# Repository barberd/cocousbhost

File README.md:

# CoCo USB Host

## Description

This board is a cartridge for the Tandy Radio Shack TRS-80 Color Computer (CoCo), an 8 bit computer produced between 1980 and 1991. It provides a USB 2.0 Host controller, the CH376S, to the CoCo. This allows one to use USB devices with the Color Computer given software drivers for the device. See "Using the Board" below.

Schematic is available [here](kicad/cocousbhost.pdf).

Assembly routines for using the cartridge in your own software can be found in the [Software](Software) directory. This includes drivers for USB hubs, keyboards, mice, and mass storage devices (such as pendrives). Additionally, a software patch for the Color Computer 3's BASIC to use a USB keyboard for input can be found in this directory.

## Building the board

This is open source hardware, so its up to one to get the board fabricated and then solder the components onto it. All components are through-hole-mount for easy assembly by hobbyists, with the exception of the CH376S chip itself; that requires surface mount soldering. 

If you've done soldering but are new to surface mounting chips: pin the chip into place by soldering two opposite corner pins, then with a hot iron and plenty of flux, run a bead of solder down each side, then wick up any excess.

### How to order for fabrication

Download [kicad/cocousbhost-fabrication.zip](kicad/cocousbhost-fabrication.zip?raw=true), then upload it to one's PCB manufacturer when asked to provide Gerber files. Usually this is found under a 'Quote' option on the website. Search "pcb manufacturing" on any major search engine to get several manufacturers. NextPCB and PCBWay are two well-known ones.

Some may have ordered boards and have extra available. Reach out to don &#x40; dgb3.net to explore this.

Use the [Bill of Materials](kicad/cocousbhost.csv) to source the components from electronic supply houses such as Mouser, Jameco, or Digi-Key.

## Source and License

Design maintained at [https://github.com/barberd/cocousbhost](https://github.com/barberd/cocousbhost). [Kicad](https://www.kicad.org/) and [Freerouting](https://github.com/freerouting/freerouting/) were used to design the board.

The design is copyright 2025 by Don Barber. The design is open source, distributed via the GNU GPL version 3 license. Please see the COPYING file for details.

## Why

In 2022 I developed the [CoCo USB Serial Pak](https://github.com/barberd/cocousbserial), a cartridge that looks like an original Tandy Deluxe RS-232 pak to the CoCo but instead presents as a USB serial device to the PC its plugged into. That cartridge allows for very fast and easy communication between the CoCo and PC (think of it as a null modem cable), but does not provide any ability to host USB devices, to the confusion of many in the CoCo community.

After that project, I wanted to produce a cartridge that did provide that USB host ability for the CoCo. I also didn't want to just interface to another computer (such as a Raspberry Pi Pico or ESP) that does the real USB work; I wanted the CoCo to control the USB bus and communicate with devices directly, recognizing I'd have to write software drivers from scratch. This is the result.

## Using the Board

Please do not expect to use this board as a drop-in to replace the Color Computer's keyboard, joysticks, storage mediums, or other hardware and expect all the original software to work immediately and transparently.

This board provides a USB bus for the Color Computer. Use of that bus, and any devices found on that bus, requires software drivers. Patches for the original DECB routines for POLCAT (read a character from the keyboard) to use a USB keyboard is available in the Software directory. These DECB patches work with most Basic programs and any machine language software coded to use DECB's built-in routines.

Conceptually, a similar patch for DECB's JOYIN (read from the Joysticks) routine can be developed, but as joysticks do not have a standard report format (unlike keyboard and mice Boot protocol), each joystick model will need a custom driver developed. But if developed, this would work for Basic programs and those machine language software packages that use the JOYIN routine.

However, the majority of original applications and games are hard-coded to access the keyboard, joystick, and serial devices directly through the Peripheral Interface Adapter (PIA) chips of the CoCo and not through DECB's provided routines. If one desires, one can patch such software to instead leverage USB devices through this cartridge, but each software package is a custom effort. One can leverage the routines and drivers in the Software directory as a starting point.

The exception for needing to patch software is when software is running under an operating system (where hardware is abstracted away through an API) and that operating system has USB drivers; the operating system's programming interface in combination with drivers takes care of the hardware interfacing. There are a few operating system available for the CoCo; see the "NitrOS-9" section below for one implementation.

To digress from this cartridge slightly: If one wants to use USB devices transparently with old software without patching, one will instead need a hardware solution that plugs directly into the original hardware's interface, presenting translated signals in a way the original software expects. This is normally done with a second computer (such as an Arduino, ESP, or Raspberry Pi Pico) doing the USB communication, converting the signal information, and then re-presenting such via the legacy interface (such as plugging into the keyboard matrix ribbon connector plug or the joystick port). See [USB to CoCo Keyboard Adapter](https://thebreakkey.com/projects.html), [PiKey](http://www.pikey.tech/), and [CocoJoyStickAdapter](https://github.com/malfunct/CocoJoystickAdapter) for examples. The [CoCoSDC](http://cocosdc.blogspot.com/) uses a similar technique with an Atmel microprocessor (though for a SD card interface, not a USB device). All these solutions are brilliant; they provide drop-in solutions requiring no change to legacy software.

The intent of this cartridge is different: unlike these hardware-interfacing solutions, this USB host cartridge provides a full USB bus to the CoCo. This means by writing new drivers, one can use any USB device, including those not originally available on the CoCo. This could include scanners, printers, webcams, network adapters, bluetooth adapters, light guns, sound adapters, digitizer drawing tablets, etc; almost any USB device can be made to work. This provides diverse flexibility for a CoCo developer to write new software leveraging a wide range of available hardware; homebrew is still alive and well for the CoCo!

Two limitations to be aware: 

  * The CH376 chip does not support isochronous USB transfers (this means some of the streaming protocols often used on sound adapters and newer webcams won't work, though many webcams still support the interrupt and bulk transfer methods as well) 
  * The CoCo itself might be too slow for some USB devices - its bus speed can only transfer data so quickly.

### Configuration

Set the 7 dip switches (SW1) for the desired base IO address. These correspond to address lines A1 through A7. The default is $FF86. See [here](https://www.cocopedia.com/wiki/index.php/External_Hardware_IO_Address_Map) for a list of known IO hardware addresses. If you happen to have a conflict, choose a different IO address, set SW1 accordingly, and reassemble binaries to match.

The orientation of SW1 matters; it should be that the 'circuit is closed' or 'on' direction points to the 0 side. This is because the 74LS682 chip works by defaulting to '1' unless pulled to ground to make it a '0'. This simplifies and lowers the cost of the address selection circuit but also results in the non-intuitive use of 'on' to get a '0' instead of a '1'.

As such, make sure to orient the switch to match 'on' to face the same direction as the '0' label. If one gets the switch upside down, not a big deal, the switch will just operate in reverse from the silkscreened labels.

### Overview

The cartridge uses two memory-mapped ports, the base address and the base address+1. The two addresses used correspond to different registers on the CH376 and board. For example, if given base address of $FF86:

  * $FF86 Data Register (Read and Write)
  * $FF87 Command Register (Write) and Flag Register (Read)

Read the [CH376 Datasheet 1](datasheets/CH376DS1.PDF?raw=true) and [CH376 Datasheet 2](datasheets/CH376DS2.PDF?raw=true) for how to use the chip.

The CH376 chip has built-in commands to access USB mass storage devices both at the block level and file level. The CH376 also allows for control transfers (used to configure devices), interrupt transfers (used for keyboards, mice, game controllers, etc), and bulk storage transfers (used for mass storage such as pendrives). It does not support isochronous transfers (used for streaming data), so it will not work with some modern sound adapters and webcam protocols.

Note that the CH376 can only connect directly to a single USB device. That device can be a USB Hub, but this means driver software must configure the hub to allow communication to other devices through it. Such a driver can be found in the Software directory. Its HIGHLY recommended to use a powered USB hub; otherwise the USB devices will draw power from the Color Computer or Multi-Pak interface.

### Interrupts

The CH376 will issue an interrupt after completing several commands. This will assert the CART\* line on the cartridge. When PIA1 is configured to do so, a fast interrupt request (FIRQ) is sent to the CPU when CART\* goes low.

To configure the PIA1 to do this, enable fast interrupts and configure it to trigger on a falling edge, like so:

                LDA     $FF23           ;load PIA1 Side B Control Register
                ORA     #$01            ;set bit 0 to 1 to enable cart firq
                ANDA    #$FD            ;set bit 1 to 0 to trigger on falling-edge
                STA     $FF23           ;store in PIA1 Side B Control Register

Hook in the interrupt handler at $010F (and/or $FEF4 on the CoCo3) as one would any other FIRQ handler. Make sure the interrupt handler performs a GET_STATUS to clear the interrupt.

If one's software doesn't handle interrupts, one will need to use software polling of the flag register instead.

See the routines in the Software directory for examples.

### ROM Socket

A socket for a ROM is also included in the board design. This is entirely optional, as many users today will instead choose to use another boot device, such as disk, SDC, or DriveWire. However, one can add a ROM loaded with a bootloader, perhaps to boot NitrOS-9 directly off a USB drive (see the "NitrOS-9" section below) or patching BASIC for USB drives and keyboards.

The ROM socket is wired for a 27128 EPROM. As the 27128 provides 16k of storage, the board presents this as 2 different banks of 8k each, selected via jumper J1. As such, when writing the EPROM, combine the images with each image aligned to an 8k boundary (eg, at 0 and 8k). If using a ROM IC other than the 27128, one will need to adjust the board design to match the chosen IC. Some other ROM ICs are pin-compatible and will work fine with the existing design.

Note Jumper J2, labeled "Autostart ROM". Color Computer cartridges signal the onboard ROM that they are present and should be started on boot by shorting the Q signal to the CART\* signal; see [Tandy Cartridge Schematic](https://colorcomputerarchive.com/repo/Documents/Manuals/Hardware/Color%20Computer%20ROM%20Cartridge%20Schematic%20%28Tandy%29.pdf). This works great for end users as game cartridges will auto-start, but this technique conflicts for device cartridges which need to also send interrupts. This is evident in cartridges like the [Tandy Deluxe RS-232 pak](https://colorcomputerarchive.com/repo/Documents/Manuals/Hardware/Deluxe%20RS-232%20Program%20Pak%20Schematic%20%28Tandy%29.pdf), wherein users had to execute the ROM manually by running "exec &hc000" (Color Computer 1 or 2) or "exec &he010" (Color Computer 3) to start their software.

Through the use of a flipflop and some additional logic, this cartridge attempts to allow auto-start while also allowing the CH376 to send interrupts after bootup: if the J2 jumper is present, then on startup, the Q signal is sent to CART\*, like any auto-start cartridge. However, once the ROM is accessed, this signal is gated off, so normal interrupts from the CH376 can be sent. This works perfectly if booting from the cartridge and allows for both auto-start and use of the CH376 interrupts.

However, if one has the J2 jumper present but boots via another method (perhaps via a floppy drive or a CocoSDC in another selected multi-pak interface slot), then the ROM is never accessed and the Q signal will continue to be asserted to CART\*. This will prevent proper use of interrupts. If one is not using the auto-start feature, remove the J2 jumper to prevent this contention.

If one never plans on using the ROM, one can eliminate components J1, J2, U7, U5, R4, and Q1.

## More Info

### NitrOS-9

[NitrOS-9](https://github.com/nitros9project/nitros9) is a community maintained open source operating system for the Color Computer based on Microware's OS9. Several modules have been written for NitrOS-9 providing a USB Manager and drivers for various USB devices (such as mass storage devices, keyboards, and mice). Additionally, a boot module is available that boots NitrOS-9 directly off a pen drive connected to this cartridge when written to a ROM in the ROM socket.

### Links

* [CH376 Datasheet 1](datasheets/CH376DS1.PDF?raw=true)
* [CH376 Datasheet 2](datasheets/CH376DS2.PDF?raw=true)
* [USB 2.0 Specification](https://www.usb.org/document-library/usb-20-specification) Useful for various control transfer protocols
* [USB HID Class Definition](https://www.usb.org/sites/default/files/documents/hid1_11.pdf) Useful Keyboard and Mouse boot protocols
* [USB Printer Device Class Definition](https://www.usb.org/sites/default/files/usbprint11a021811.pdf) 
* [USB Mass Storage Specification](https://www.usb.org/sites/default/files/Mass_Storage_Specification_Overview_v1.4_2-19-2010.pdf)
* [USB Mass Storage Bulk-Only Transport](https://www.usb.org/sites/default/files/usbmassbulk_10.pdf)
* [SCSI Command Reference (from Seagate)](https://www.seagate.com/files/staticfiles/support/docs/manual/Interface%20manuals/100293068j.pdf) USB Mass storage devices use encapsulated SCSI
* [Color Computer Technical Reference](https://colorcomputerarchive.com/repo/Documents/Manuals/Hardware/Color%20Computer%20Technical%20Reference%20Manual%20%28Tandy%29.pdf) See Page 18 of the manual/25 of the PDF for bus timings.

### Note on the CH375B versus CH376S

The CH375 is a very similar chip that provides the same USB functionality of the CH376. The CH376 also costs slightly more and its additional features (interfacing with an SD card controller) are not used on this cartridge. Therefore, one might be tempted to use a CH375 instead. 

In the author's experience, the CH375 has an undocumented bug that drops a byte seemingly at random, leading to corrupted data and trouble keeping software and hardware in sync. This behavior was consistent across four chips the author tested, and seems consistent with anecdotal user experiences found online around other solutions using the CH375, such as ISA cards designed for early PCs.

If one does choose to use the CH375B instead, either add a bodge wire or modify the design before manufacturing to connect pin 23 to ground, and use $2B (WR_USB_DATA7) for the write command instead of $2C (WR_HOST_DATA).

## Errata

None at this time.

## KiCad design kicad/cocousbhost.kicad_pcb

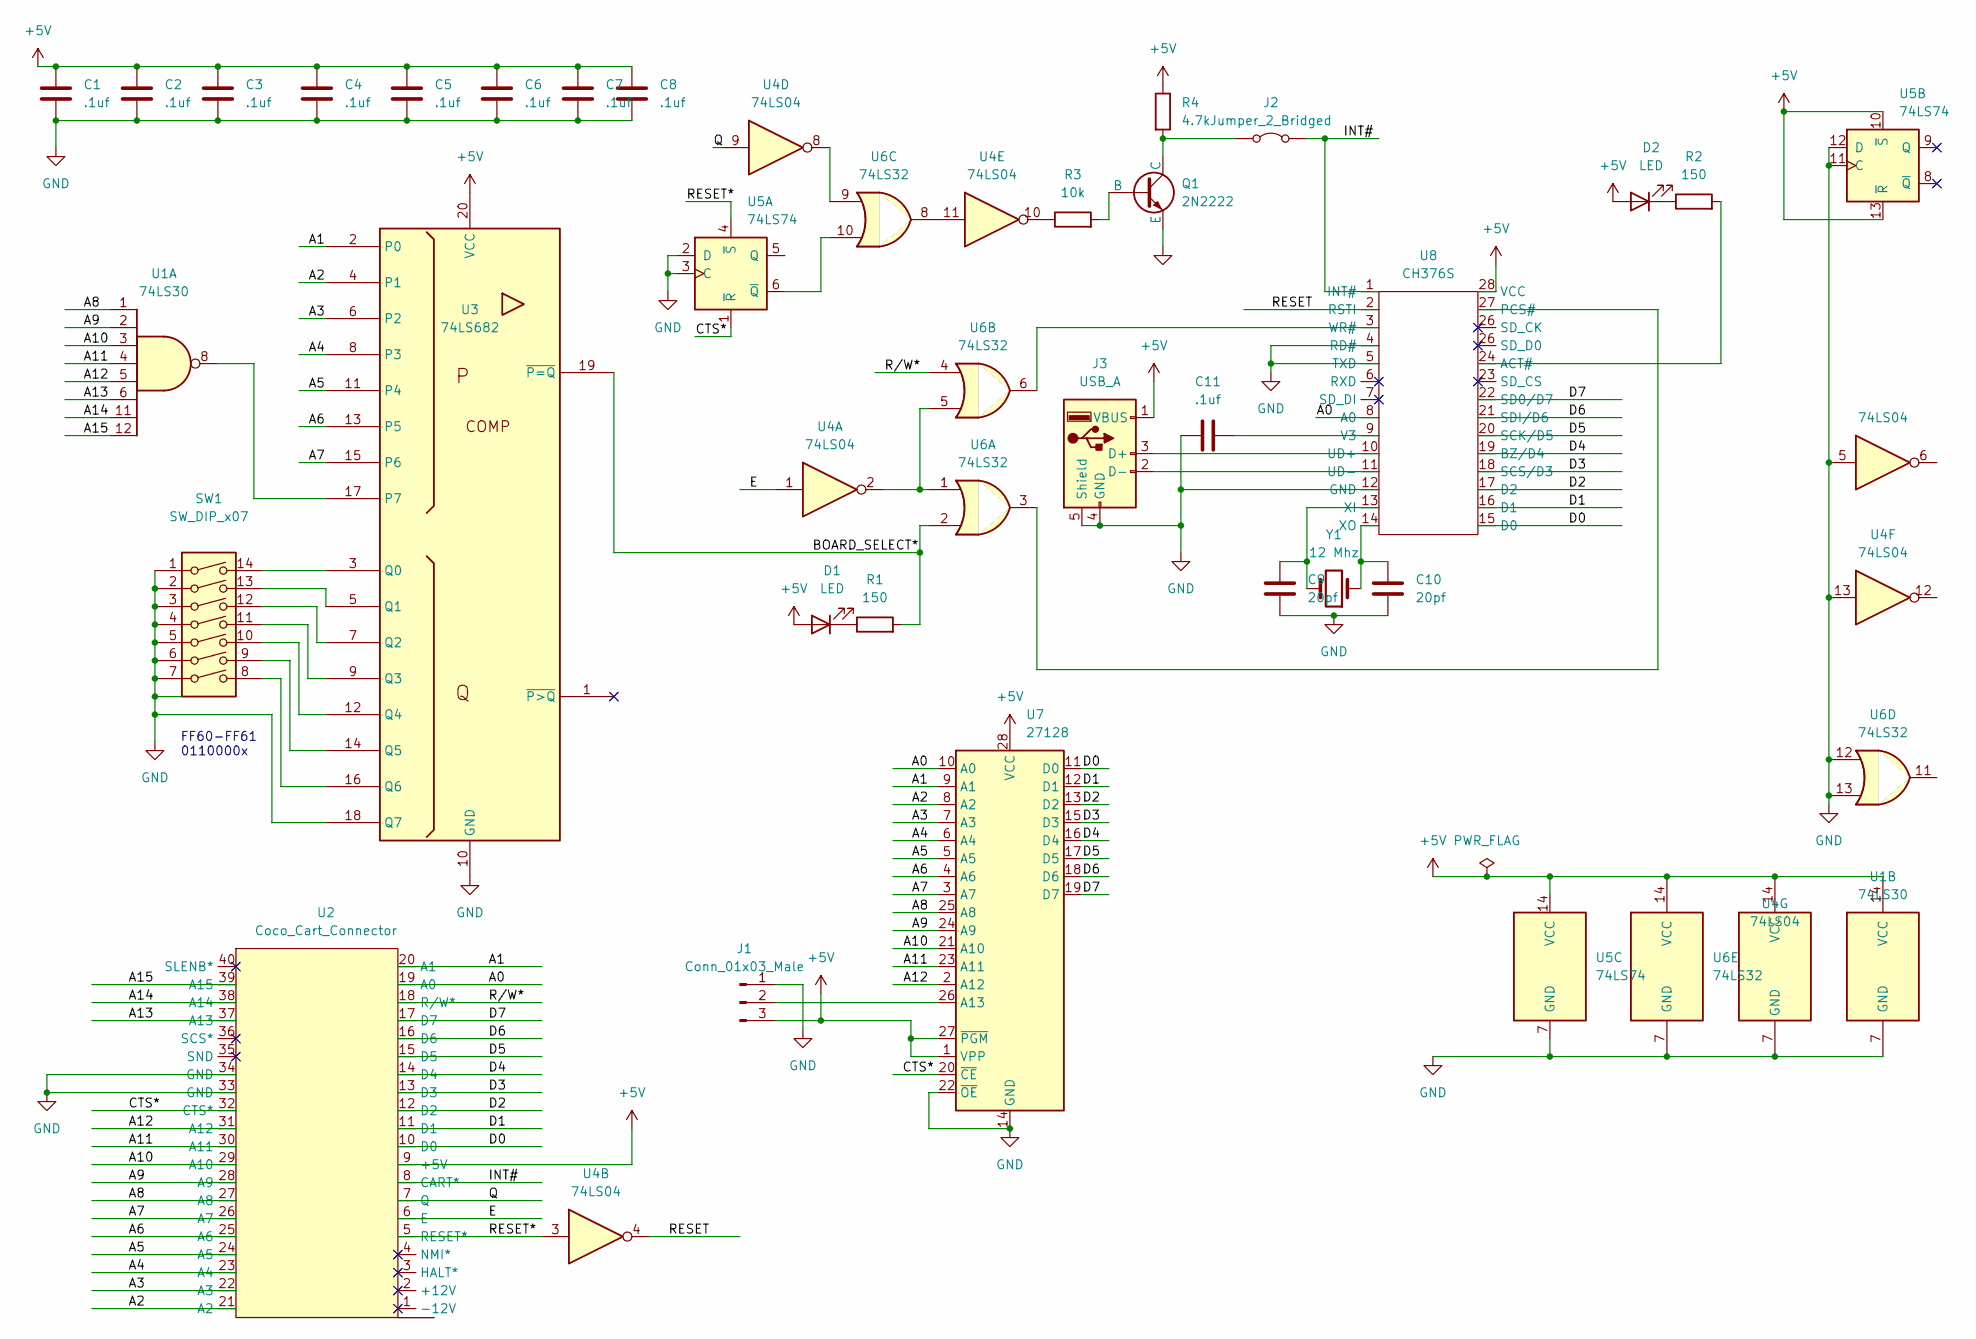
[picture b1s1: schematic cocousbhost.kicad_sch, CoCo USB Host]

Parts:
C1, C2, C3, C4, C5, C6, C7, C8, C11: .1uf; C_Disc_D6.0mm_W2.5mm_P5.00mm
C9, C10: 20pf; C_Disc_D6.0mm_W2.5mm_P5.00mm
D1, D2: LED; LED_D3.0mm
J1: Conn_01x03_Male; PinHeader_1x03_P2.54mm_Vertical
J2: Jumper_2_Bridged; PinHeader_1x02_P2.54mm_Vertical
J3: USB_A; USB_A_Molex_67643_Horizontal
Q1: 2N2222; TO-92
R1, R2: 150; R_Axial_DIN0204_L3.6mm_D1.6mm_P7.62mm_Horizontal
R3: 10k; R_Axial_DIN0204_L3.6mm_D1.6mm_P7.62mm_Horizontal
R4: 4.7k; R_Axial_DIN0204_L3.6mm_D1.6mm_P7.62mm_Horizontal
SW1: SW_DIP_x07; SW_DIP_SPSTx07_Slide_6.7x19.34mm_W7.62mm_P2.54mm_LowProfile
U1: 74LS30; DIP-14_W7.62mm
U2: Coco_Cart_Connector; Coco_Cart
U3: 74LS682; DIP-20_W7.62mm
U4: 74LS04; DIP-14_W7.62mm
U5: 74LS74; DIP-14_W7.62mm
U6: 74LS32; DIP-14_W7.62mm
U7: 27128; DIP-28_W15.24mm
U8: CH376S; SOP-28
Y1: 12 Mhz; Crystal_HC52-8mm_Vertical

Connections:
+5V: C1.1, C2.1, C3.1, C4.1, C5.1, C6.1, C7.1, C8.1, D1.2 (A), D2.2 (A), J1.3, J3.1 (VBUS), R4.1, U1.14 (VCC), U2.9 (+5V), U3.20 (VCC), U4.14 (VCC), U5.10 (~S), U5.13 (~R), U5.14 (VCC), U6.14 (VCC), U7.1 (VPP), U7.27 (~PGM), U7.28 (VCC), U8.28 (VCC)
/A0: U2.19 (A0), U7.10 (A0), U8.8 (A0)
/A1: U2.20 (A1), U3.2 (P0), U7.9 (A1)
/A2: U2.21 (A2), U3.4 (P1), U7.8 (A2)
/A3: U2.22 (A3), U3.6 (P2), U7.7 (A3)
/A4: U2.23 (A4), U3.8 (P3), U7.6 (A4)
/A5: U2.24 (A5), U3.11 (P4), U7.5 (A5)
/A6: U2.25 (A6), U3.13 (P5), U7.4 (A6)
/A7: U2.26 (A7), U3.15 (P6), U7.3 (A7)
/A8: U1.1, U2.27 (A8), U7.25 (A8)
/A9: U1.2, U2.28 (A9), U7.24 (A9)
/A10: U1.3, U2.29 (A10), U7.21 (A10)
/A11: U1.4, U2.30 (A11), U7.23 (A11)
/A12: U1.5, U2.31 (A12), U7.2 (A12)
/A13: U1.6, U2.37 (A13)
/A14: U1.11, U2.38 (A14)
/A15: U1.12, U2.39 (A15)
/BOARD_SELECT*: R1.2, U3.19 (~P=Q), U6.2
/CTS*: U2.32 (CTS*), U5.1 (~R), U7.20 (~CE)
/D0: U2.10 (D0), U7.11 (D0), U8.15 (D0)
/D1: U2.11 (D1), U7.12 (D1), U8.16 (D1)
/D2: U2.12 (D2), U7.13 (D2), U8.17 (D2)
/D3: U2.13 (D3), U7.15 (D3), U8.18 (SCS/D3)
/D4: U2.14 (D4), U7.16 (D4), U8.19 (BZ/D4)
/D5: U2.15 (D5), U7.17 (D5), U8.20 (SCK/D5)
/D6: U2.16 (D6), U7.18 (D6), U8.21 (SDI/D6)
/D7: U2.17 (D7), U7.19 (D7), U8.22 (SD0/D7)
/E: U2.6 (E), U4.1
/INT#: J2.2 (B), U2.8 (CART*), U8.1 (INT#)
/Q: U2.7 (Q), U4.9
/RESET: U4.4, U8.2 (RSTI)
/RESET*: U2.5 (RESET*), U4.3, U5.4 (~S)
/R/W*: U2.18 (R/W*), U6.4
GND: C1.2, C2.2, C3.2, C4.2, C5.2, C6.2, C7.2, C8.2, C9.1, C10.1, C11.1, J1.1, J3.4 (GND), J3.5 (Shield), Q1.3 (E), SW1.1, SW1.2, SW1.3, SW1.4, SW1.5, SW1.6, SW1.7, U1.7 (GND), U2.33 (GND), U2.34 (GND), U3.10 (GND), U3.18 (Q7), U4.5, U4.7 (GND), U4.13, U5.2 (D), U5.3 (C), U5.7 (GND), U5.11 (C), U5.12 (D), U6.7 (GND), U6.12, U6.13, U7.14 (GND), U7.22 (~OE), U8.4 (RD#), U8.5 (TXD), U8.12 (GND)
unnamed: D1.1 (K), R1.1
unnamed: D2.1 (K), R2.1
unnamed: J1.2, U7.26 (A13)
unnamed: J2.1 (A), Q1.1 (C), R4.2
unnamed: J3.3 (D+), U8.10 (UD+)
unnamed: J3.2 (D-), U8.11 (UD-)
unnamed: Q1.2 (B), R3.2
unnamed: R3.1, U4.10
unnamed: U1.8, U3.17 (P7)
unnamed: SW1.14, U3.3 (Q0)
unnamed: SW1.13, U3.5 (Q1)
unnamed: SW1.12, U3.7 (Q2)
unnamed: SW1.11, U3.9 (Q3)
unnamed: SW1.10, U3.12 (Q4)
unnamed: SW1.9, U3.14 (Q5)
unnamed: SW1.8, U3.16 (Q6)
unnamed: U4.2, U6.1, U6.5
unnamed: U4.8, U6.9
unnamed: U4.11, U6.8
unnamed: U5.6 (~Q), U6.10
unnamed: R2.2, U8.24 (ACT#)
unnamed: U6.3, U8.27 (PCS#)
unnamed: C11.2, U8.9 (V3)
unnamed: U6.6, U8.3 (WR#)
unnamed: C9.2, U8.13 (XI), Y1.2
unnamed: C10.2, U8.14 (XO), Y1.1

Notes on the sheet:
FF60-FF61 0110000x

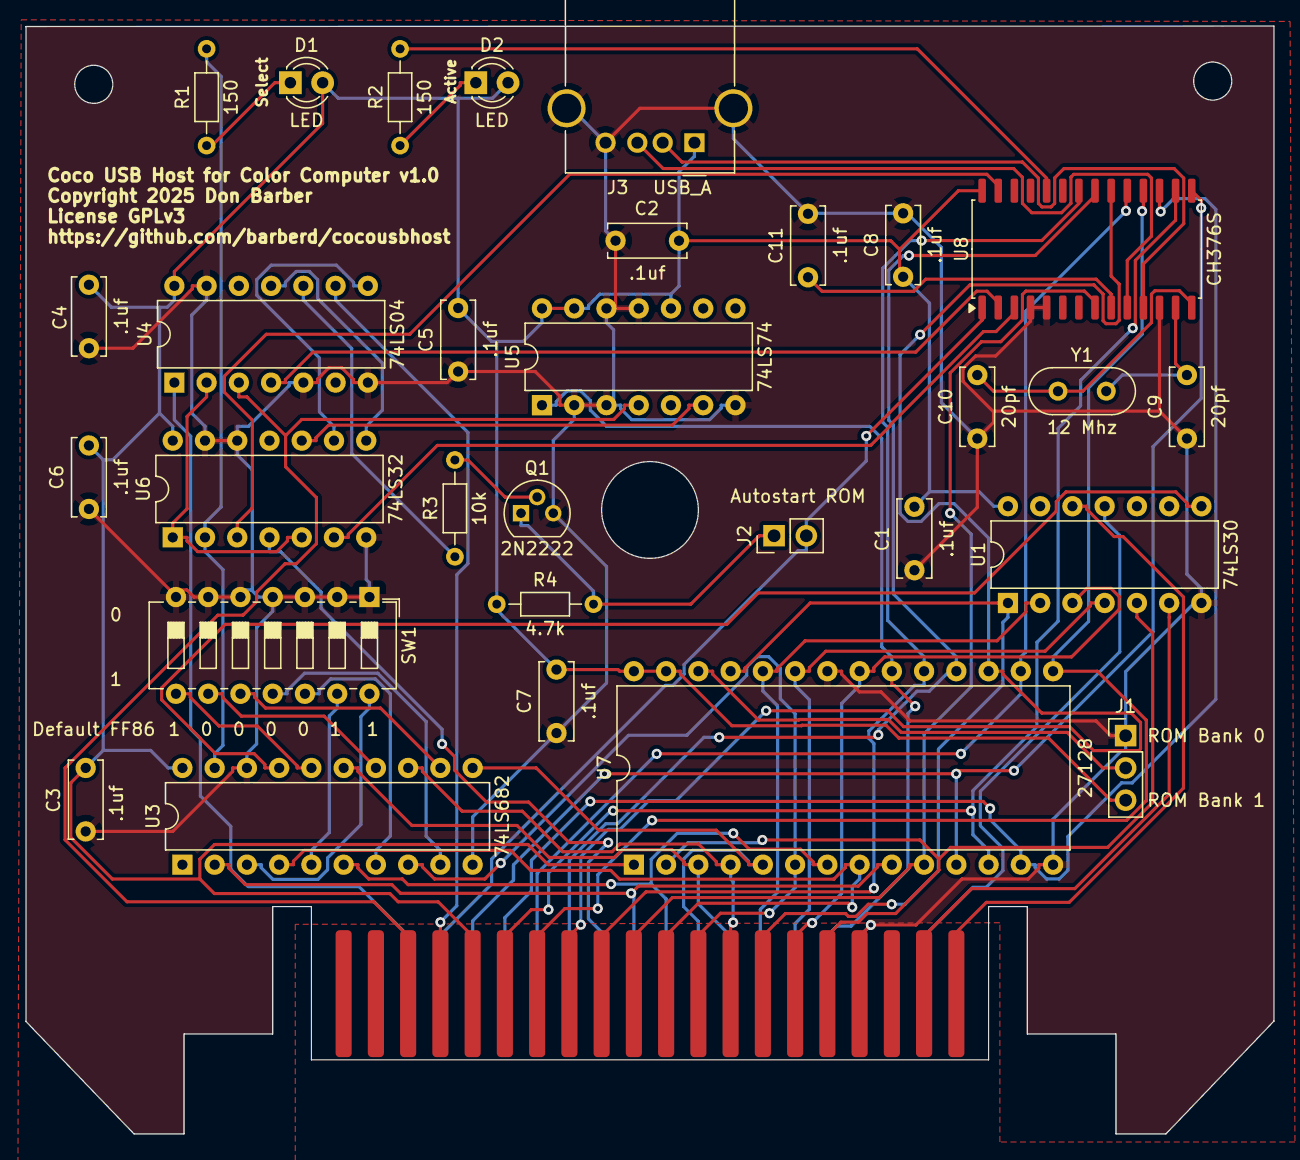
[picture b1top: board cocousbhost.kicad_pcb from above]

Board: 2 copper layers, 98.3 x 87.3 mm, 31 parts (0 on the bottom side), 60 nets.

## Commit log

2025-02-17 Added schematic of PDF
2025-02-17 Fixed some grammar
2025-02-23 Renamed to CoCo USB Host
2025-02-23 Removed old csv
2025-02-23 Updated fabrication link
2025-02-23 Added Printer Device Class Link
2025-02-24 Updated notes on isochronous transfers

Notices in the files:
kicad/cocousbhost.kicad_pcb:
Copyright 2025 Don Barber
License GPLv3
kicad/cocousbhost.kicad_sch:
Licensed GPL v3
